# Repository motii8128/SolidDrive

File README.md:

# SolidDrive
This is a project to develop a custom motor driver.

# OverView

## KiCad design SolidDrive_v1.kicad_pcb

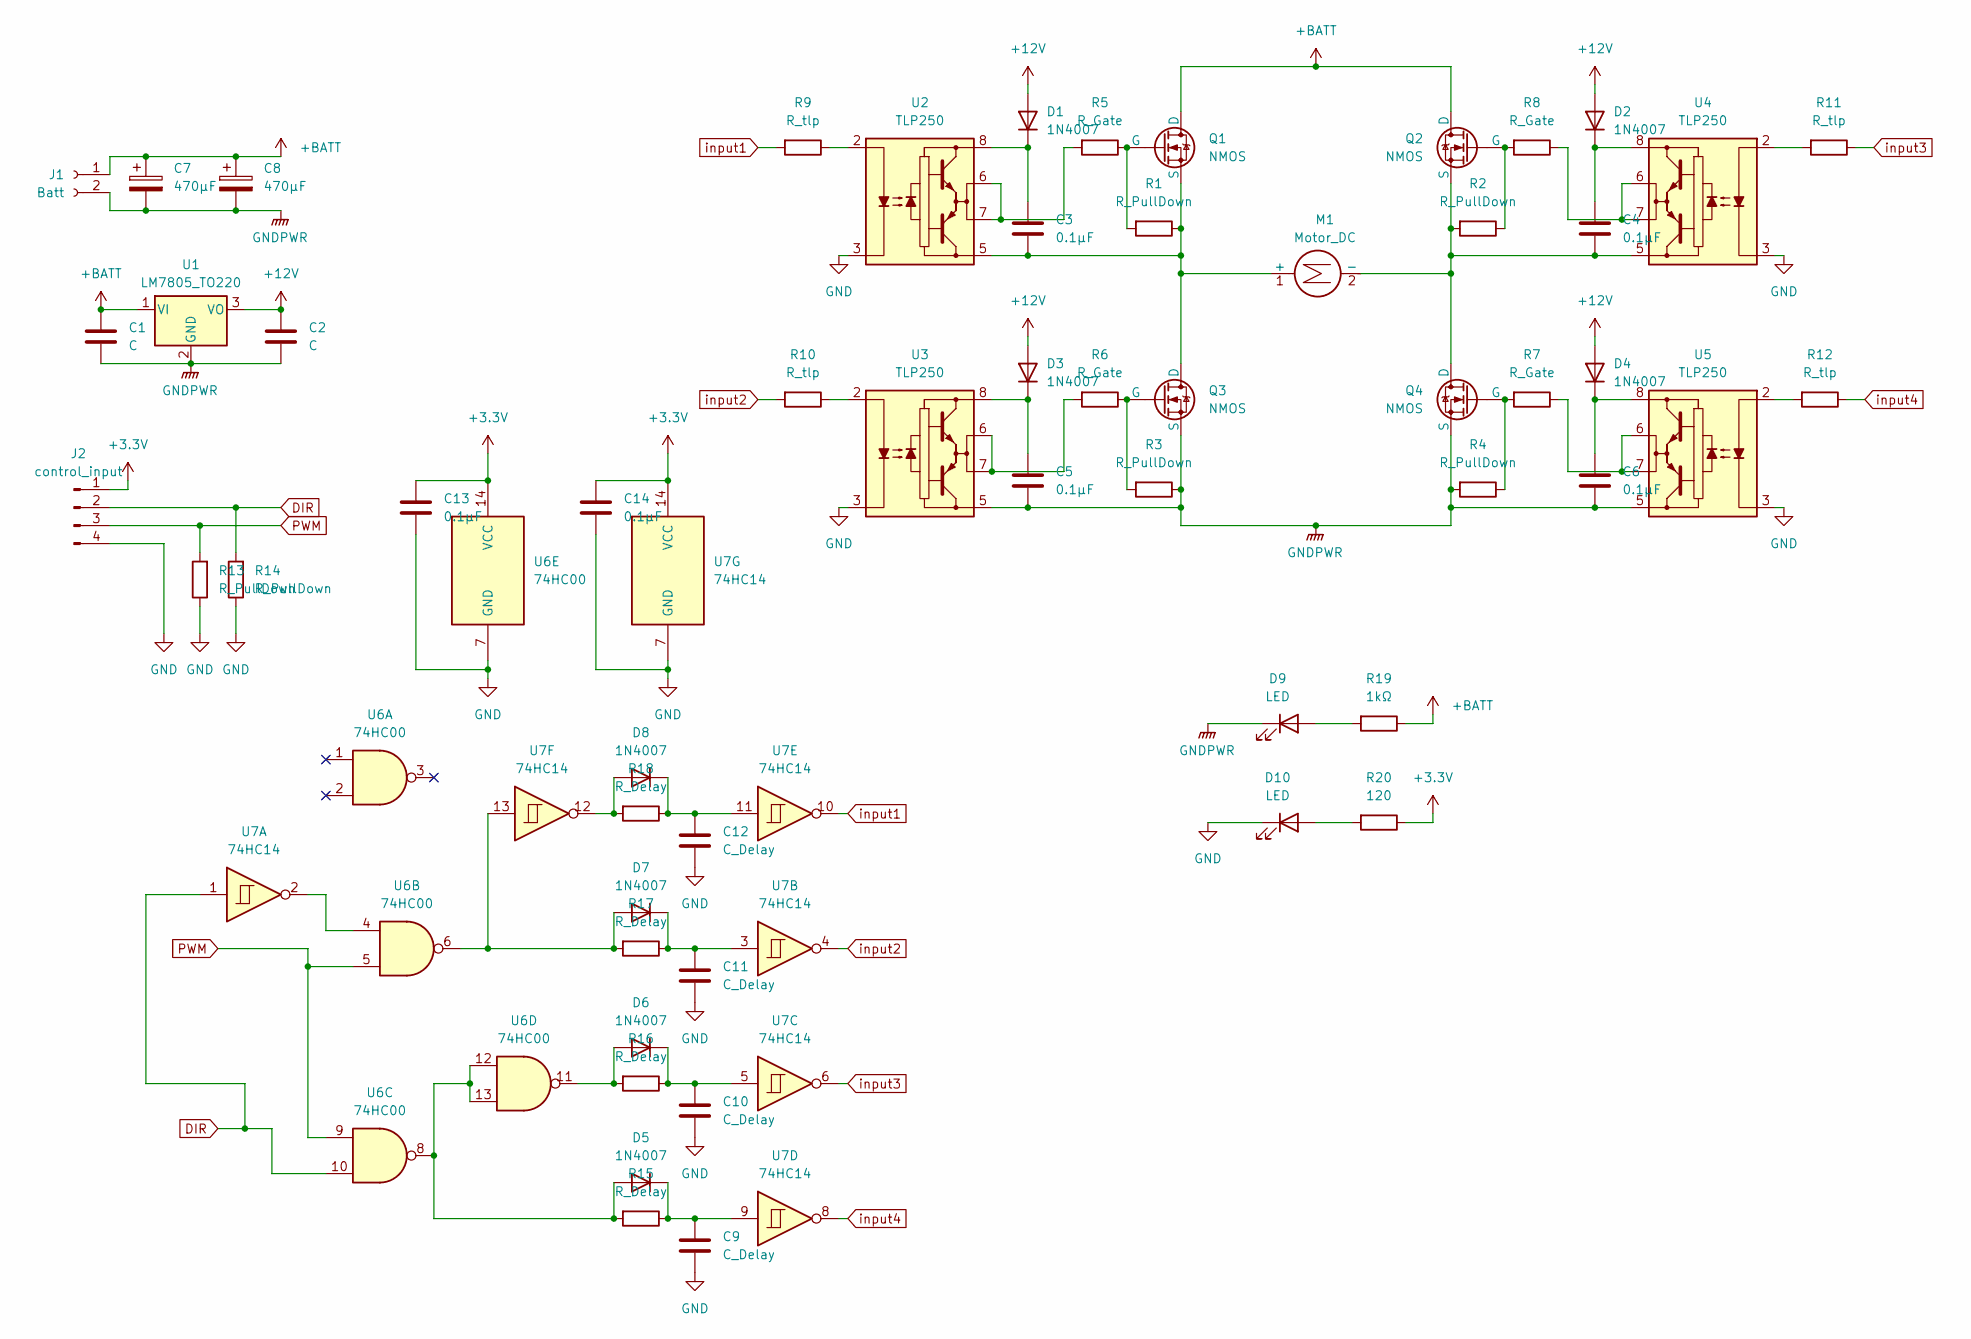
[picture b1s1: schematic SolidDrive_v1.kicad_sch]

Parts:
C1, C2: C; C_Disc_D3.0mm_W1.6mm_P2.50mm
C3, C4, C5, C6, C13, C14: 0.1μF; C_Disc_D3.0mm_W1.6mm_P2.50mm
C7, C8: 470μF; CP_Radial_D10.0mm_P7.50mm
C9, C10, C11, C12: C_Delay; C_Disc_D3.0mm_W1.6mm_P2.50mm
D1, D2, D3, D4, D5, D6, D7, D8: 1N4007; D_DO-41_SOD81_P10.16mm_Horizontal
D9, D10: LED; LED_D3.0mm
J1: Batt; AMASS_XT30PW-M_1x02_P2.50mm_Horizontal
J2: control_input; PinHeader_1x04_P2.54mm_Horizontal
M1: Motor_DC; AMASS_XT30PW-F_1x02_P2.50mm_Horizontal
Q1, Q2, Q3, Q4: NMOS; TO-220-3_Horizontal_TabUp
R1, R2, R3, R4, R13, R14: R_PullDown; R_Axial_DIN0207_L6.3mm_D2.5mm_P10.16mm_Horizontal
R5, R6, R7, R8: R_Gate; R_Axial_DIN0207_L6.3mm_D2.5mm_P10.16mm_Horizontal
R9, R10, R11, R12: R_tlp; R_Axial_DIN0207_L6.3mm_D2.5mm_P10.16mm_Horizontal
R15, R16, R17, R18: R_Delay; R_Axial_DIN0207_L6.3mm_D2.5mm_P10.16mm_Horizontal
R19: 1kΩ; R_Axial_DIN0207_L6.3mm_D2.5mm_P10.16mm_Horizontal
R20: 120; R_Axial_DIN0207_L6.3mm_D2.5mm_P10.16mm_Horizontal
U1: LM7805_TO220; TO-252-2
U2, U3, U4, U5: TLP250; DIP-8_W7.62mm
U6: 74HC00; DIP-14_W7.62mm
U7: 74HC14; DIP-14_W7.62mm

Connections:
+3.3V: C13.1, C14.1, J2.1, R20.1, U6.14 (VCC), U7.14 (VCC)
+12V: C2.1, D1.2 (A), D2.2 (A), D3.2 (A), D4.2 (A), U1.3 (VO)
+BATT: C1.1, C7.1, C8.1, J1.1, Q1.1 (D), Q2.1 (D), R19.1, U1.1 (VI)
DIR: J2.2, R14.2, U6.10, U7.1
GND: C9.2, C10.2, C11.2, C12.2, C13.2, C14.2, D10.1 (K), J2.4, R13.1, R14.1, U2.3 (C), U3.3 (C), U4.3 (C), U5.3 (C), U6.7 (GND), U7.7 (GND); also elsewhere on the board
GNDPWR: C1.2, C2.2, C5.2, C6.2, C7.2, C8.2, D9.1 (K), J1.2, Q3.3 (S), Q4.3 (S), R3.1, R4.2, U1.2 (GND), U3.5 (VEE), U5.5 (VEE); also elsewhere on the board
unnamed: C3.1, D1.1 (K), U2.8 (VCC)
unnamed: C4.1, D2.1 (K), U4.8 (VCC)
unnamed: C5.1, D3.1 (K), U3.8 (VCC)
unnamed: C6.1, D4.1 (K), U5.8 (VCC)
unnamed: D5.2 (A), R15.2, U6.8, U6.12, U6.13
unnamed: C9.1, D5.1 (K), R15.1, U7.9
unnamed: D6.2 (A), R16.2, U6.11
unnamed: C10.1, D6.1 (K), R16.1, U7.5
unnamed: D7.2 (A), R17.2, U6.6, U7.13
unnamed: C11.1, D7.1 (K), R17.1, U7.3
unnamed: D8.2 (A), R18.2, U7.12
unnamed: C12.1, D8.1 (K), R18.1, U7.11
unnamed 18: D9.2 (A), R19.2; also elsewhere on the board
unnamed 19: D10.2 (A), R20.2; also elsewhere on the board
unnamed: C3.2, M1.1 (+), Q1.3 (S), Q3.1 (D), R1.1, U2.5 (VEE)
unnamed: C4.2, M1.2 (-), Q2.3 (S), Q4.1 (D), R2.2, U4.5 (VEE)
unnamed: Q1.2 (G), R1.2, R5.1
unnamed: Q2.2 (G), R2.1, R8.2
unnamed: Q3.2 (G), R3.2, R6.1
unnamed: Q4.2 (G), R4.1, R7.2
unnamed: R5.2, U2.6 (VO), U2.7 (VO)
unnamed: R6.2, U3.6 (VO), U3.7 (VO)
unnamed: R7.1, U5.6 (VO), U5.7 (VO)
unnamed: R8.1, U4.6 (VO), U4.7 (VO)
unnamed: R9.1, U2.2 (A)
unnamed: R10.1, U3.2 (A)
unnamed: R11.2, U4.2 (A)
unnamed: R12.2, U5.2 (A)
unnamed: U6.4, U7.2
PWM: J2.3, R13.2, U6.5, U6.9
input1: R9.2, U7.10
input2: R10.2, U7.4
input3: R11.1, U7.6
input4: R12.1, U7.8

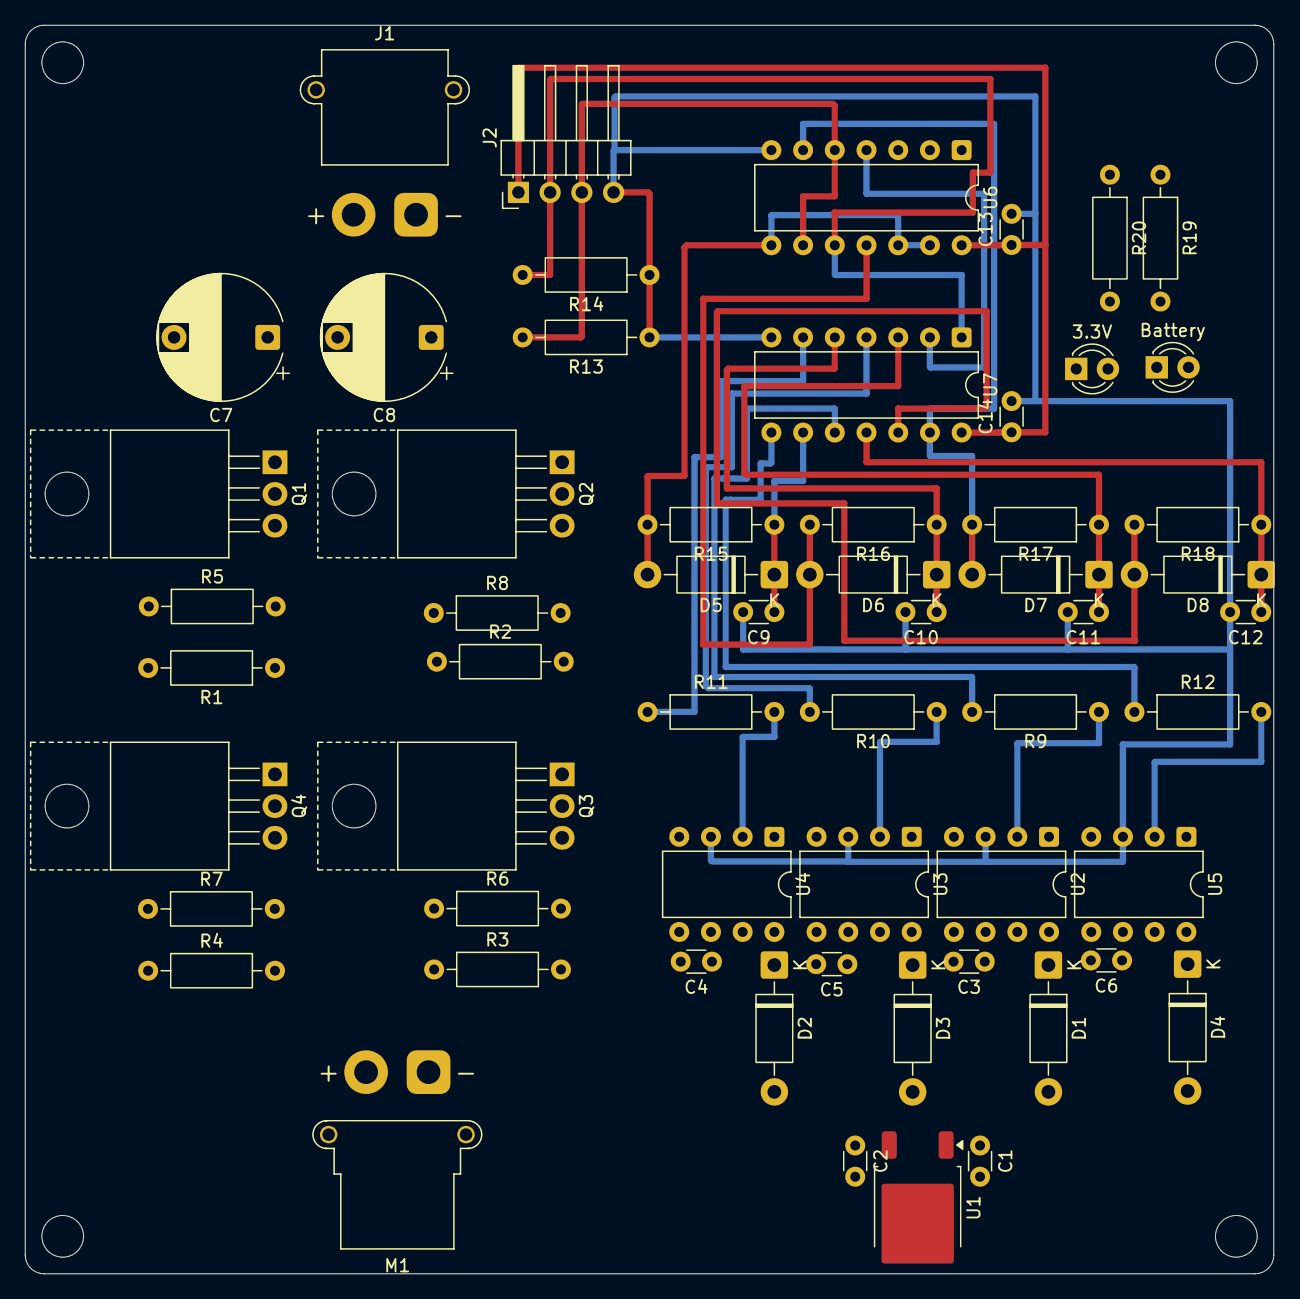
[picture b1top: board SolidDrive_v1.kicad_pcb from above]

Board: 2 copper layers, 100.0 x 100.0 mm, 58 parts (0 on the bottom side), 40 nets.

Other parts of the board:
3.3V: LED; LED_D3.0mm
Battery: LED; LED_D3.0mm

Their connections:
GND: 3.3V.1 (K); also elsewhere on the board
GNDPWR: Battery.1 (K); also elsewhere on the board
unnamed 18: Battery.2 (A); also elsewhere on the board
unnamed 19: 3.3V.2 (A); also elsewhere on the board

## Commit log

2025-07-19 completed power circuit
2025-07-19 [update] complete power cuircuit
2025-07-20 [update] complete logic circuit
2025-07-21 [update] complete logic circuit placement
2025-07-21 [update] complete gate driver placement
2025-07-25 [udpate] complete part position
2025-07-25 [update] upload circuit image
